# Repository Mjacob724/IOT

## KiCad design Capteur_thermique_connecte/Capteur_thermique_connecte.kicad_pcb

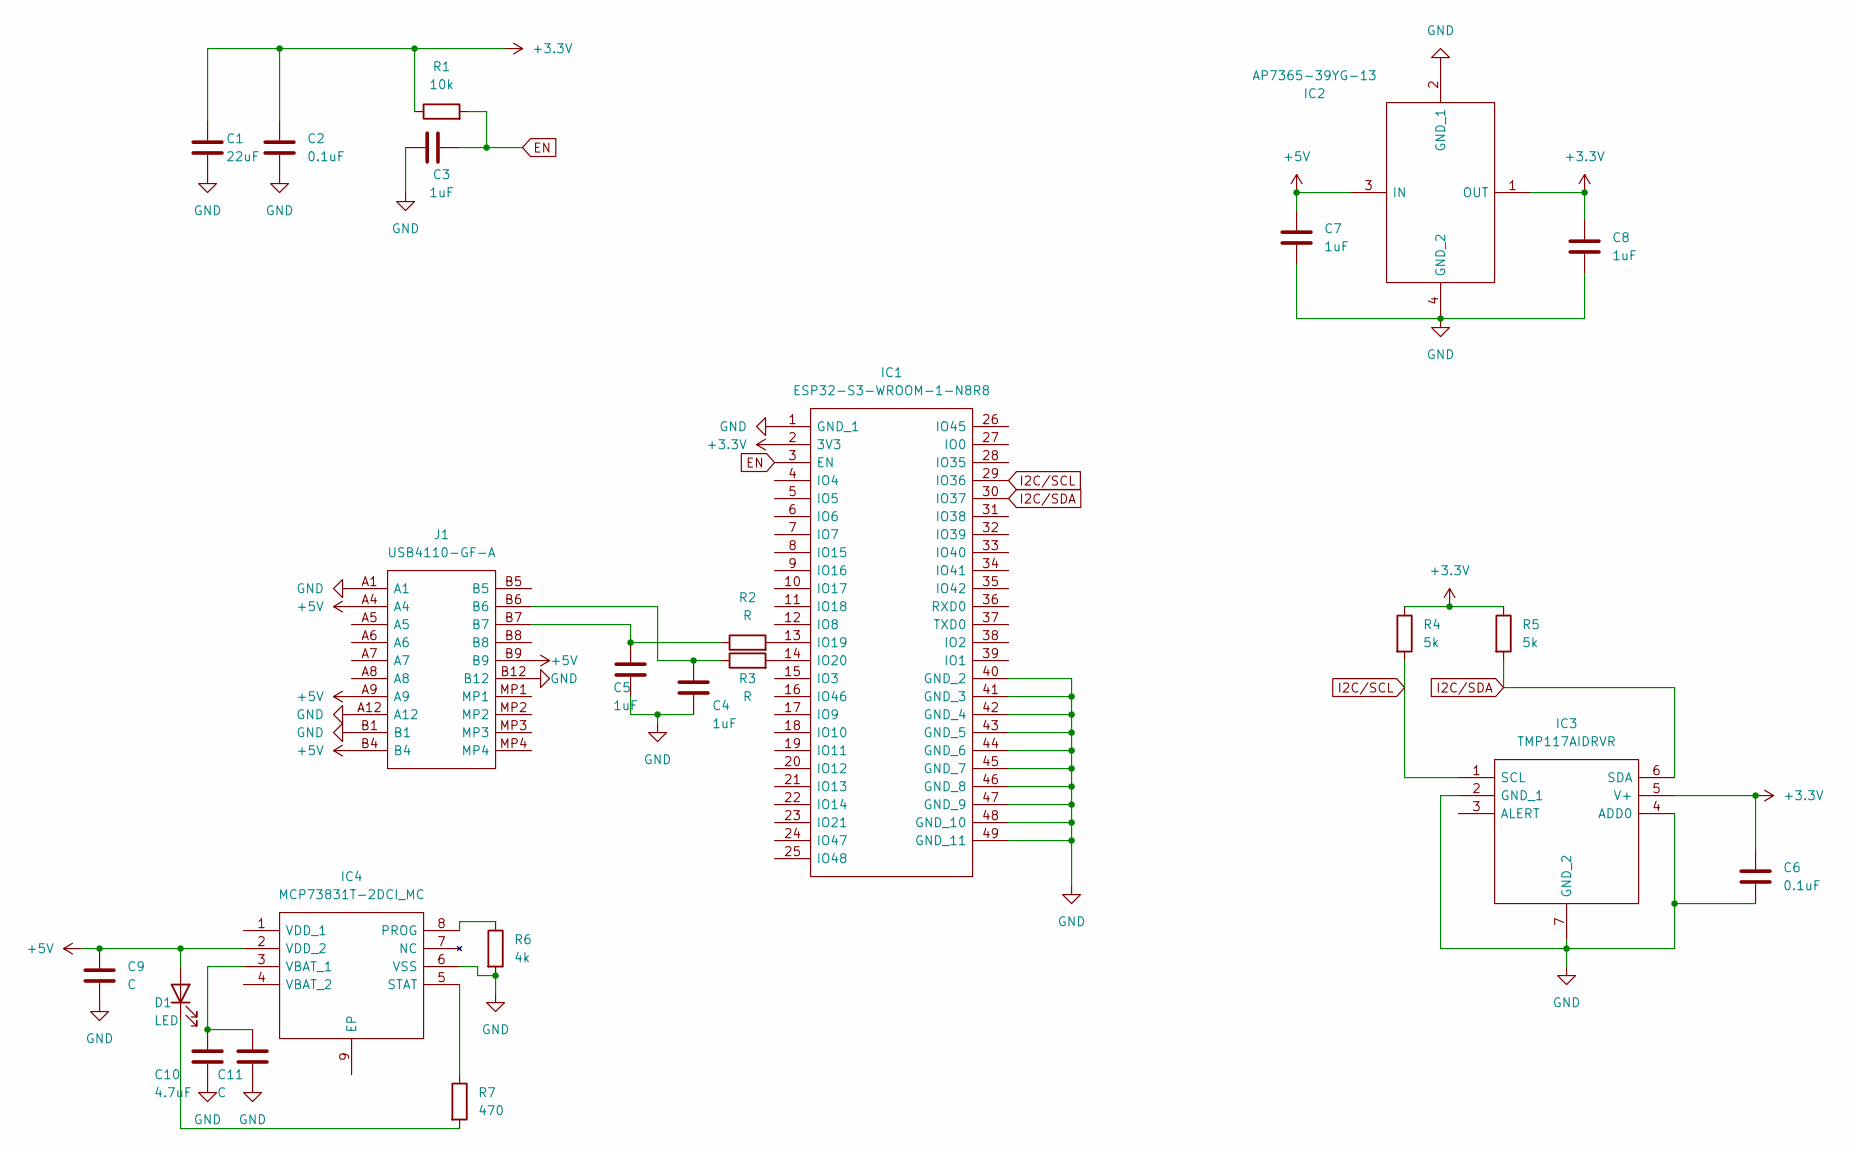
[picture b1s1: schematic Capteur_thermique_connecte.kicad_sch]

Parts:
C1: 22uF; C_0805_2012Metric
C2, C6: 0.1uF; C_0805_2012Metric
C3, C4, C5, C7, C8: 1uF; C_0805_2012Metric
C9, C11: C; C_0805_2012Metric
C10: 4.7uF; C_0805_2012Metric
D1: LED; LED_0805_2012Metric
IC1: ESP32-S3-WROOM-1-N8R8; ESP32S3WROOM1N8R8; Manufacturer_Part_Number ESP32-S3-WROOM-1-N8R8; Mouser Part Number 356-EP32S3WROOM1N8R8
IC2: AP7365-39YG-13; AP736539YG13; Manufacturer_Part_Number AP7365-39YG-13; Mouser Part Number 621-AP7365-39YG-13
IC3: TMP117AIDRVR; SON65P200X200X80-7N; Manufacturer_Part_Number TMP117AIDRVR; Mouser Part Number 595-TMP117AIDRVR
IC4: MCP73831T-2DCI_MC; SON50P300X200X100-9N-D; Manufacturer_Part_Number MCP73831T-2DCI/MC; Mouser Part Number 579-MCP73831T-2DCIMC
J1: USB4110-GF-A; USB4110GFA; Manufacturer_Part_Number USB4110-GF-A; Mouser Part Number 640-USB4110-GF-A
R1: 10k; R_0805_2012Metric
R2, R3: R; R_0805_2012Metric
R4, R5: 5k; R_0805_2012Metric
R6: 4k; R_0805_2012Metric
R7: 470; R_0805_2012Metric

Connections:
+3.3V: C1.1, C2.1, C6.1, C8.1, IC1.2 (3V3), IC2.1 (OUT), IC3.5 (V+), R1.1, R4.1, R5.1
+5V: C7.1, C9.2, D1.2 (A), IC2.3 (IN), IC4.2 (VDD_2), J1.A4, J1.A9, J1.B4, J1.B9
EN: C3.1, IC1.3 (EN), R1.2
GND: C1.2, C2.2, C3.2, C4.2, C5.2, C6.2, C7.2, C8.2, C9.1, C10.2, C11.2, IC1.1 (GND_1), IC1.40 (GND_2), IC1.41 (GND_3), IC1.42 (GND_4), IC1.43 (GND_5), IC1.44 (GND_6), IC1.45 (GND_7), IC1.46 (GND_8), IC1.47 (GND_9), IC1.48 (GND_10), IC1.49 (GND_11), IC2.2 (GND_1), IC2.4 (GND_2), IC3.2 (GND_1), IC3.4 (ADD0), IC3.7 (GND_2), IC4.6 (VSS), J1.A1, J1.A12, J1.B1, J1.B12, R6.2; also elsewhere on the board
I2C/SCL: IC1.29 (IO36), IC3.1 (SCL), R4.2
I2C/SDA: IC1.30 (IO37), IC3.6 (SDA), R5.2
unnamed: C4.1, J1.B6, R3.1
unnamed: C5.1, J1.B7, R2.1
unnamed: D1.1 (K), R7.2
unnamed: IC1.13 (IO19), R2.2
unnamed: IC1.14 (IO20), R3.2
unnamed: IC4.8 (PROG), R6.1
unnamed: IC4.5 (STAT), R7.1
unnamed 13: C10.1, C11.1, IC4.3 (VBAT_1); also elsewhere on the board

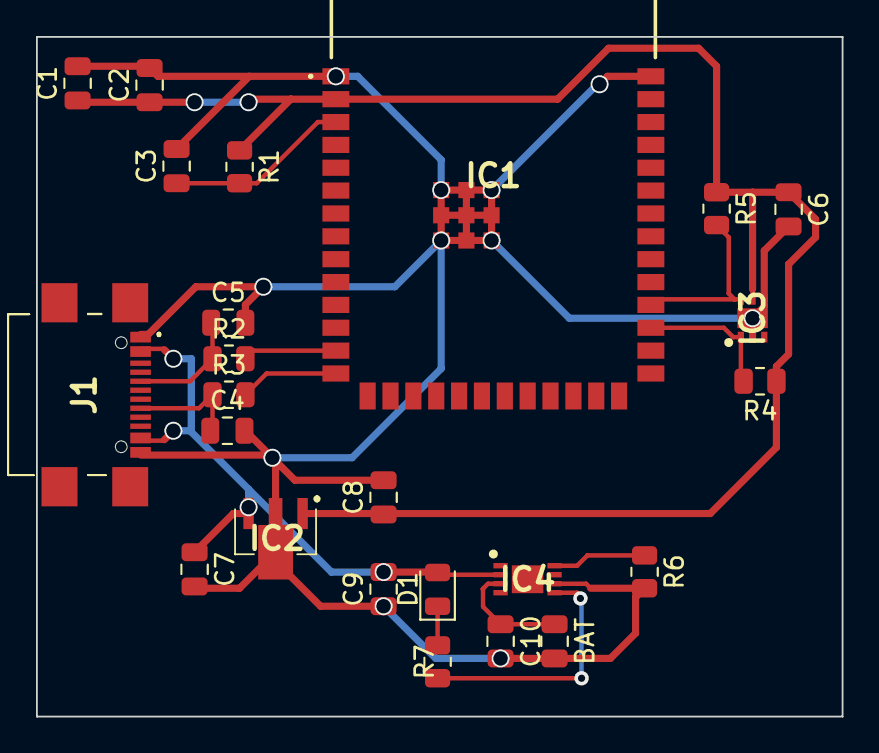
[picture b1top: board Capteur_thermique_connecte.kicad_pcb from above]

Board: 2 copper layers, 44.8 x 37.8 mm, 24 parts (0 on the bottom side), 14 nets.

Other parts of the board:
BAT: C; C_0805_2012Metric

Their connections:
GND: BAT.2; also elsewhere on the board
unnamed 13: BAT.1; also elsewhere on the board

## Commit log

2023-10-25 Upload projet PCB
